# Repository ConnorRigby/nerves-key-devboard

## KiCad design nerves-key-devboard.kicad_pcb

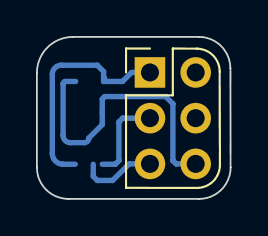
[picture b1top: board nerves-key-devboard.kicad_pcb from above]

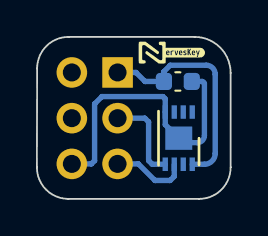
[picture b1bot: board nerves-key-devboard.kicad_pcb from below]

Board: 2 copper layers, 10.8 x 9.0 mm, 4 parts (3 on the bottom side), 4 nets.

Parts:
C1: C_0402_100nf_X7R; C_0603_1608Metric
J1: Raspberry_Pi_2_3; PinHeader_2x03_P2.54mm_Vertical
U1: ATECC608A-MAHDA-S; DFN-8-1EP_3x2mm_P0.5mm_EP1.3x1.5mm
kibuzzard-64A6D6EE: G***; kibuzzard-64A6D6EE

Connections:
/I2C_SDA: J1.3 (SDA/GPIO2), U1.5 (SDA)
GND: C1.2, J1.6 (GND), U1.4 (GND), U1.9 (EP)
unnamed: J1.5 (SCL/GPIO3), U1.6 (SCL)
VCC: C1.1, J1.1 (3V3), U1.8 (VCC)
